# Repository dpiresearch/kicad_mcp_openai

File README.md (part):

# Discussions. Get in here.

https://github.com/mixelpixx/KiCAD-MCP-Server/discussions/73

# KiCAD MCP Server

A Model Context Protocol (MCP) server that enables AI assistants like OpenAI Codex to interact with KiCAD for PCB design automation. Built on the MCP 2025-06-18 specification, this server provides comprehensive tool schemas and real-time project state access for intelligent PCB design workflows.

## Overview

The [Model Context Protocol](https://modelcontextprotocol.io/) is an open standard that allows AI assistants to securely connect to external tools and data sources. This implementation provides a standardized bridge between OpenAI-powered MCP clients and KiCAD, enabling natural language control of PCB design operations.

**Key Capabilities:**

- 122 tools across 16 categories with JSON Schema validation
- Smart tool discovery with router pattern (reduces AI context by 70%)
- 8 dynamic resources exposing project state
- Complete schematic workflow with 27 tools and dynamic symbol loading (~10,000 symbols)
- Freerouting autorouter integration (Java, Docker, or Podman)
- Custom footprint and symbol creation tools
- JLCPCB parts integration with 2.5M+ component catalog and local library search
- Datasheet enrichment via LCSC
- Full MCP 2025-06-18 protocol compliance
- Cross-platform support (Linux, Windows, macOS)
- Real-time KiCAD UI integration via IPC API (experimental)
- Comprehensive error handling and logging

## Try out Arduino MCP - now you can get OpenAI Codex to help in the IDE, real time!:

https://github.com/mixelpixx/arduino-ide

## What's New in v2.2.3

### New Tools: FFC/Ribbon Cable Passthrough Workflow

A complete workflow for designing passthrough adapter boards (e.g. Raspberry Pi CSI
cable adapters) is now supported:

1. `connect_passthrough` — wires all pins of one connector to the matching pins of
   another in the schematic (J1 pin N → J2 pin N, auto-named nets).
2. `sync_schematic_to_board` — imports the net assignments into the PCB.
3. `route_pad_to_pad` — routes each connection with automatic via insertion when
   pads are on opposite copper layers.
4. `snapshot_project` — saves a named checkpoint into `<project>/snapshots/`.

### Bug Fixes (KiCAD 9 / Windows)

- **Via insertion for B.Cu footprints** — `route_pad_to_pad` now correctly detects
  when a footprint is on B.Cu and inserts the required via. (KiCAD 9 SWIG returned
  `F.Cu` for all SMD pads regardless of layer — fixed.)
- **Board outline rounded corners** — `add_board_outline` now correctly applies
  `cornerRadius` when `shape="rounded_rectangle"`.
- **B.Cu placement hang** — placing a footprint on B.Cu no longer causes a ~30s
  freeze in KiCAD 9.

### Developer Mode

Set `KICAD_MCP_DEV=1` in your Codex MCP server environment to automatically save
the MCP session log into the project's `logs/` folder on every `export_gerber` and
`snapshot_project` call. Useful for debugging and for attaching to GitHub issues.

```json
"env": {
  "KICAD_MCP_DEV": "1"
}
```

> **Privacy warning:** The session log contains your full tool call history
> (including file paths and design details). **Review or delete `logs/` before
> sharing a project directory publicly.**

See [CHANGELOG](CHANGELOG.md) for the full list of changes in this release.

---

## What's New in v2.1.0

### Critical Schematic Workflow Fix + Complete Wiring System (Issue #26)

The schematic workflow was completely broken in previous versions - **this is now fixed AND dramatically enhanced!**

**What was broken:**

- `create_project` only created PCB files, no schematics
- `add_schematic_component` called non-existent API methods
- Schematics couldn't be created or edited at all
- Only 13 component types available (severe limitation)
- No working wire/connection functionality

**Complete Implementation (3 Phases):**

**Phase 1: Component Placement Foundation**

- `create_project` now creates both .kicad_pcb and .kicad_sch files
- Added pre-configured template schematics with 13 common component types
- Rewrote component placement to use proper `clone()` API

**Phase 2: Dynamic Symbol Loading (BREAKTHROUGH!)**

- **Access to ALL ~10,000 KiCad symbols** from standard libraries
- Automatic detection and dynamic loading from `.kicad_sym` library files
- Zero configuration required - just specify library and symbol name
- Seamless integration with existing MCP tools
- Full S-expression parsing and injection system

**Phase 3: Intelligent Wiring System (NEW in v2.1.0)**

- **Automatic pin location discovery** with rotation support (0°, 90°, 180°, 270°)
- **Smart wire routing** (direct, orthogonal horizontal-first, orthogonal vertical-first)
- **Power symbol support** (VCC, GND, +3V3, +5V, etc.)
- **Wire graph analysis** - geometric tracing for net connectivity
- **Net label management** (local, global, hierarchical labels)
- **Netlist generation** with accurate component/pin connections

**Technical Architecture:**
The kicad-skip library cannot create symbols or wires from scratch. We implemented a comprehensive solution:

1. **Static Templates:** 13 pre-configured symbols (R, C, L, LED, etc.) for instant use
2. **Dynamic Loading:** On-demand injection of ANY symbol from KiCad libraries:
   - Parse `.kicad_sym` library files using S-expression parser
   - Inject symbol definition into schematic's `lib_symbols` section
   - Create offscreen template instance
   - Reload schematic so kicad-skip sees new template
   - Clone template to create actual component
3. **Wire Creation:** S-expression-based wire injection (bypasses kicad-skip API limitations)
4. **Pin Discovery:** Parse symbol definitions, apply rotation transformations, calculate absolute positions
5. **Connectivity Analysis:** Geometric wire tracing to build net connection graphs

**Example - Complete Circuit Creation:**

```python
# Load power symbols dynamically
loader.load_symbol_dynamically(sch_path, "power", "VCC")

# Place components with auto-rotation
ComponentManager.add_component(sch, {
    "type": "STM32F103C8Tx",
    "library": "MCU_ST_STM32F1",
    "reference": "U1",
    "x": 100, "y": 100, "rotation": 0
})

# Connect with intelligent routing
ConnectionManager.add_connection(sch_path, "U1", "1", "R1", "2", routing="orthogonal_h")

# Connect to power nets
ConnectionManager.connect_to_net(sch_path, "U1", "VDD", "VCC")

# Analyze connectivity
connections = ConnectionManager.get_net_connections(sch, "VCC", sch_path)
# Returns: [{"component": "U1", "pin": "VDD"}, {"component": "R1", "pin": "1"}]
```

**Test Results:**

- Component placement: 100% passing
- Dynamic symbol loading: 10,000+ symbols accessible
- Wire creation: 100% passing (8/8 connections in test circuit)
- Pin discovery: Rotation-aware, sub-millimeter accuracy
- Net connectivity: 100% accurate (VCC: 2 connections, GND: 4 connections)
- Netlist generation: Working with accurate pin-level connections

See [Schematic Tools Reference](docs/SCHEMATIC_TOOLS_REFERENCE.md) for the complete schematic tool documentation.

### IPC Backend (Experimental)

We are currently implementing and testing the KiCAD 9.0 IPC API for real-time UI synchronization:

- Changes made via MCP tools appear immediately in the KiCAD UI
- No manual reload required when IPC is active
- Hybrid backend: uses IPC when available, falls back to SWIG API
- IPC runtime reconnect: if MCP has fallen back to SWIG, IPC-capable board
  tools retry IPC after KiCAD launches instead of staying on SWIG for the entire
  session
- 20+ commands now support IPC including routing, component placement, and zone operations

Note: IPC features are under active development and testing. Enable IPC in KiCAD via Preferences > Plugins > Enable IPC API Server.

For OpenCode on Windows, the backend can be configured as `auto`, `ipc`, or
`swig` during setup. See [OpenCode (Windows)](#opencode-windows) for the
configuration command and backend options.

### Tool Discovery & Router Pattern

We've implemented an intelligent tool router to keep AI context efficient while maintaining full functionality:

- **18 direct tools** always visible for high-frequency operations
- **65 routed tools** organized into 8 categories (board, component, export, drc, schematic, library, routing, autoroute)
- **35 additional tools** always visible (symbol/footprint creators, JLCPCB, datasheet, advanced routing)
- **4 router tools** for discovery and execution:
  - `list_tool_categories` - Browse all available categories
  - `get_category_tools` - View tools in a specific category
  - `search_tools` - Find tools by keyword
  - `execute_tool` - Run any tool with parameters

**Why this matters:** By organizing tools into discoverable categories, OpenAI Codex can intelligently find and use the right tool for your task without loading all 122 tool schemas into every conversation. This reduces context consumption while maintaining full access to all functionality.

**Usage is seamless:** Just ask naturally - "export gerber files" or "add mounting holes" - and Codex will discover and execute the appropriate tools automatically.

### NEEDS TESTING - REPORT ISSUES

### JLCPCB Parts Integration (New!)

Complete integration with JLCPCB's parts catalog, providing two complementary approaches for component selection:

**Dual-Mode Architecture:**

1. **Local Symbol Libraries** - Search JLCPCB libraries installed via KiCAD Plugin and Content Manager (contributed by [@l3wi](https://github.com/l3wi))
2. **JLCPCB API Integration** - Access the complete 2.5M+ parts catalog with real-time pricing and stock data

**Key Features:**

- Real-time pricing with quantity breaks (1+, 10+, 100+, 1000+)
- Stock availability checking
- Basic vs Extended library type identification (Basic = free assembly)
- Intelligent cost optimization with alternative part suggestions
- Package-to-footprint mapping for KiCAD compatibility
- Parametric search by category, package, manufacturer
- Local SQLite database for fast offline searching
- No API credentials required for local library search

**Why this matters:** JLCPCB offers PCB assembly services where Basic parts have no assembly fee, while Extended parts charge $3 per unique component. This integration helps you find the cheapest components with the best availability, potentially saving hundreds of dollars on assembly costs for production runs.

See [JLCPCB Usage Guide](docs/JLCPCB_USAGE_GUIDE.md) for detailed setup and usage instructions.

### Comprehensive Tool Schemas

Every tool now includes complete JSON Schema definitions with:

- Detailed parameter descriptions and constraints
- Input validation with type checking
- Required vs. optional parameter specifications
- Enumerated values for categorical inputs
- Clear documentation of what each tool does

### Resources Capability

Access project state without executing tools:

- `kicad://project/current/info` - Project metadata
- `kicad://project/current/board` - Board properties
- `kicad://project/current/components` - Component list (JSON)
- `kicad://project/current/nets` - Electrical nets
- `kicad://project/current/layers` - Layer stack configuration
- `kicad://project/current/design-rules` - Current DRC settings
- `kicad://project/current/drc-report` - Design rule violations
- `kicad://board/preview.png` - Board visualization (PNG)

### Protocol Compliance

- Updated to MCP SDK 1.21.0 (latest)
- Full JSON-RPC 2.0 support
- Proper capability negotiation
- Standards-compliant error codes

## Available Tools

The server provides **122 tools** organized into 16 functional categories. With the router pattern, tools are automatically discovered as needed -- just ask Codex what you want to accomplish.

For the complete tool reference with access types (direct/routed/additional), see [Tool Inventory](docs/TOOL_INVENTORY.md).

### Project Management (5 tools)

- `create_project` - Initialize new KiCAD projects
- `open_project` - Load existing project files
- `save_project` - Save current project state
- `get_project_info` - Retrieve project metadata
- `snapshot_project` - Save named checkpoint snapshot

### Board Operations (12 tools)

- `set_board_size` - Configure PCB dimensions
- `add_board_outline` - Create board edge (rectangle, circle, polygon, rounded rectangle)
- `add_layer` - Add custom layers to stack
- `set_active_layer` - Switch working layer
- `get_layer_list` - List all board layers
- `get_board_info` - Retrieve board properties
- `get_board_2d_view` - Generate board preview image
- `capture_design_snapshot` - Save schematic and PCB visual snapshots for review
- `get_board_extents` - Get board bounding box
- `add_mounting_hole` - Place mounting holes
- `add_board_text` - Add text annotations
- `add_zone` - Add copper zone/pour with clearance settings
- `import_svg_logo` - Import SVG file as PCB silkscreen polygons

### Component Management (16 tools)

- `place_component` - Place single component with footprint
- `move_component` - Reposition existing component
- `rotate_component` - Rotate component by angle
- `delete_component` - Remove component from board
- `edit_component` - Modify component properties
- `find_component` - Search by reference or value
- `get_component_properties` - Query component details
- `add_component_annotation` - Add annotation/comment
- `group_components` - Group multiple components
- `replace_component` - Replace with different footprint
- `get_component_pads` - Get all pad information
- `get_component_list` - List all placed components
- `get_pad_position` - Get precise pad position
- `place_component_array` - Create component grids/patterns
- `align_components` - Align multiple components
- `duplicate_component` - Copy existing component

### Routing (13 tools)

- `add_net` - Create electrical net
- `route_trace` - Route copper traces between XY points
- `route_pad_to_pad` - Route between pads with auto-via insertion
- `add_via` - Place vias for layer transitions
- `delete_trace` - Remove traces (by UUID, position, or net)
- `query_traces` - Query/filter traces
- `get_nets_list` - List all nets with statistics
- `modify_trace` - Change trace width, layer, or net
- `create_netclass` - Define net class with rules
- `add_copper_pour` - Create copper zones/pours
- `route_differential_pair` - Route differential signals
- `refill_zones` - Refill all copper zones
- `copy_routing_pattern` - Replicate routing between component groups

### Schematic (27 tools)

Complete schematic workflow with dynamic symbol loading (~10,000 symbols) and intelligent wiring.

**Component Operations:**

- `add_schematic_component` - Place symbols from any KiCad library
- `delete_schematic_component` - Remove component
- `edit_schematic_component` - Edit footprint, value, reference, label positions, and **arbitrary custom properties** (MPN, Manufacturer, DigiKey_PN, LCSC, Voltage, Tolerance, Dielectric, …) in one batched call
- `set_schematic_component_property` - Add or update a single custom property (BOM/sourcing field) on a component
- `remove_schematic_component_property` - Delete a single custom property from a component
- `get_schematic_component` - Inspect every field on a component (built-in + custom) including label positions
- `list_schematic_components` - List all components
- `move_schematic_component` - Reposition component
- `rotate_schematic_component` - Rotate component
- `annotate_schematic` - Auto-assign reference designators

**Wiring and Connections:**

- `add_wire` - Create wire between points
- `delete_schematic_wire` - Remove wire segment
- `add_schematic_connection` - Auto-connect pins with routing
- `add_schematic_net_label` - Add net labels (VCC, GND, signals)
- `delete_schematic_net_label` - Remove net label
- `connect_to_net` - Connect pin to named net
- `connect_passthrough` - Wire all matching pins between connectors (FFC/ribbon)
- `get_schematic_pin_locations` - Get pin locations for component

**Analysis and Export:**

- `get_net_connections` - Trace net connectivity
- `list_schematic_nets` / `list_schematic_wires` / `list_schematic_labels`
- `create_schematic` - Create new schematic file
- `get_schematic_view` - Rasterized schematic preview
- `export_schematic_svg` / `export_schematic_pdf`
- `run_erc` - Electrical rule check
- `generate_netlist` - Generate netlist from schematic
- `sync_schematic_to_board` - Import nets/pads to PCB (F8 equivalent)

See [Schematic Tools Reference](docs/SCHEMATIC_TOOLS_REFERENCE.md) for details and examples.

### Design Rules / DRC (8 tools)

- `set_design_rules` / `get_design_rules` - Configure and inspect rules
- `run_drc` - Execute design rule check
- `get_drc_violations` - Get violation list by severity
- `add_net_class` / `assign_net_to_class` - Net class management
- `set_layer_constraints` / `check_clearance` - Layer and clearance rules

### Export (8 tools)

- `export_gerber` - Gerber fabrication files
- `export_pdf` / `export_svg` - Documentation and vector graphics
- `export_3d` - 3D models (STEP, STL, VRML, OBJ)
- `export_bom` - Bill of materials (CSV, XML, HTML, JSON)
- `export_netlist` - Netlist (KiCad, Spice, Cadstar, OrcadPCB2)
- `export_position_file` - Component positions for pick and place
- `export_vrml` - VRML 3D model

### Footprint Libraries (4 tools) and Symbol Libraries (4 tools)

- `list_libraries` / `list_symbol_libraries` - Browse available libraries
- `search_footprints` / `search_symbols` - Search across all libraries
- `list_library_footprints` / `list_library_symbols` - Browse specific library
- `get_footprint_info` / `get_symbol_info` - Detailed information

### Footprint Creator (4 tools) and Symbol Creator (4 tools)

Create custom components when existing libraries do not have what you need.

- `create_footprint` / `create_symbol` - Build from scratch with pads/pins
- `edit_footprint_pad` - Modify pad properties
- `register_footprint_library` / `register_symbol_library` - Register in lib-table
- `list_footprint_libraries` / `list_symbols_in_library` - Browse custom libraries
- `delete_symbol` - Remove symbol from library

See [Footprint and Symbol Creator Guide](docs/FOOTPRINT_SYMBOL_CREATOR_GUIDE.md) for details.

### Datasheet Tools (2 tools)

- `enrich_datasheets` - Auto-populate datasheet URLs using LCSC part numbers
- `get_datasheet_url` - Get LCSC datasheet URL for a component

### JLCPCB Integration (5 tools)

- `download_jlcpcb_database` - Download 2.5M+ parts catalog (one-time setup)
- `search_jlcpcb_parts` - Search with parametric filters
- `get_jlcpcb_part` - Detailed part info with pricing
- `get_jlcpcb_database_stats` - Database statistics
- `suggest_jlcpcb_alternatives` - Find cheaper or in-stock alternatives

### Freerouting Autorouter (4 tools)

- `autoroute` - Run Freerouting autorouter (DSN export, route, SES import)
- `export_dsn` / `import_ses` - Manual Specctra DSN/SES workflow
- `check_freerouting` - Verify Java and Freerouting availability

See [Freerouting Guide](docs/FREEROUTING_GUIDE.md) for setup and usage.

### UI Management (2 tools)

- `check_kicad_ui` - Check if KiCAD is running
- `launch_kicad_ui` - Launch KiCAD application

## Prerequisites

### Required Software

**KiCAD 9.0 or higher**

- Download from [kicad.org/download](https://www.kicad.org/download/)
- Must include Python module (pcbnew)
- Verify installation:
  ```bash
  python3 -c "import pcbnew; print(pcbnew.GetBuildVersion())"
  ```

**Node.js 18 or Higher**

- Download from [nodejs.org](https://nodejs.org/)
- Verify: `node --version` and `npm --version`

**Python 3.9 or Higher**

- Comes bundled with KiCAD (macOS builds ship Python 3.9; Linux/Windows builds ship Python 3.11)
- Required packages (auto-installed):
  - kicad-python (kipy) >= 0.5.0 (IPC API support, optional but recommended)
  - kicad-skip >= 0.1.0 (schematic support)
  - Pillow >= 9.0.0 (image processing)
  - cairosvg >= 2.7.0 (SVG rendering)
  - colorlog >= 6.7.0 (logging)
  - pydantic >= 2.5.0 (validation)
  - requests >= 2.32.5 (HTTP client)
  - python-dotenv >= 1.0.0 (environment)

**MCP Client**
Choose one:

- [OpenAI Codex CLI](https://developers.openai.com/codex) - Official OpenAI CLI with MCP support
- [Cline](https://github.com/cline/cline) - VSCode extension
- [OpenCode](https://opencode.ai/) - Terminal-based AI coding agent with MCP support

### Supported Platforms

- **Linux** (Ubuntu 22.04+, Fedora, Arch) - Primary platform, fully tested
- **Windows 10/11** - Fully supported with automated setup
- **macOS** - Experimental support

## Installation

### Linux (Ubuntu/Debian)

```bash
# Install KiCAD 9.0 or higher
sudo add-apt-repository --yes ppa:kicad/kicad-9.0-releases
sudo apt-get update
sudo apt-get install -y kicad kicad-libraries

# Install Node.js
curl -fsSL https://deb.nodesource.com/setup_20.x | sudo -E bash -
sudo apt-get install -y nodejs

# Clone and build
git clone https://github.com/mixelpixx/KiCAD-MCP-Server.git
cd KiCAD-MCP-Server
npm install
pip3 install -r requirements.txt
npm run build

# Verify
python3 -c "import pcbnew; print(pcbnew.GetBuildVersion())"
```

### Windows 10/11

**Automated Setup (Recommended):**

```powershell
git clone https://github.com/mixelpixx/KiCAD-MCP-Server.git
cd KiCAD-MCP-Server
.\setup-windows.ps1
```

The script will:

- Detect KiCAD installations, including both machine-wide installs under
  `C:\Program Files\KiCad` and per-user installs under
  `%LOCALAPPDATA%\Programs\KiCad`
- Verify prerequisites
- Install dependencies
- Build project
- Generate configuration
- Run diagnostics

**Manual Setup:**
See [Windows Installation Guide](docs/WINDOWS_SETUP.md) for detailed instructions.

### macOS

**Important:** On macOS, use KiCAD's bundled Python to ensure proper access to the `pcbnew` module.

#### Manual Setup

```bash
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
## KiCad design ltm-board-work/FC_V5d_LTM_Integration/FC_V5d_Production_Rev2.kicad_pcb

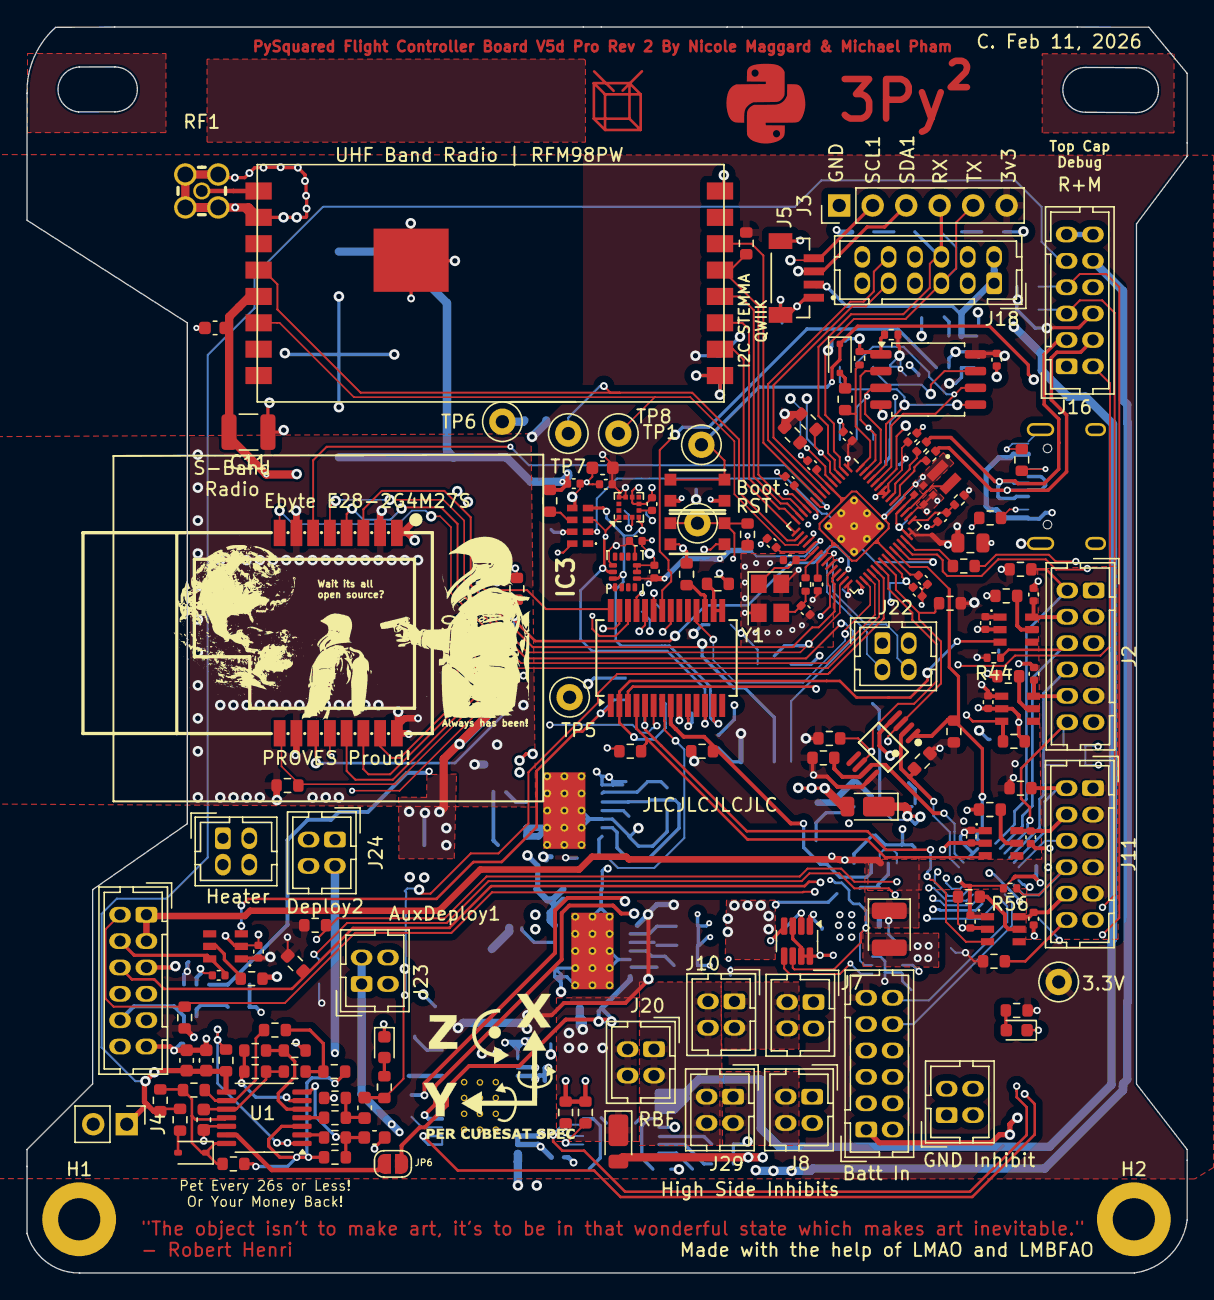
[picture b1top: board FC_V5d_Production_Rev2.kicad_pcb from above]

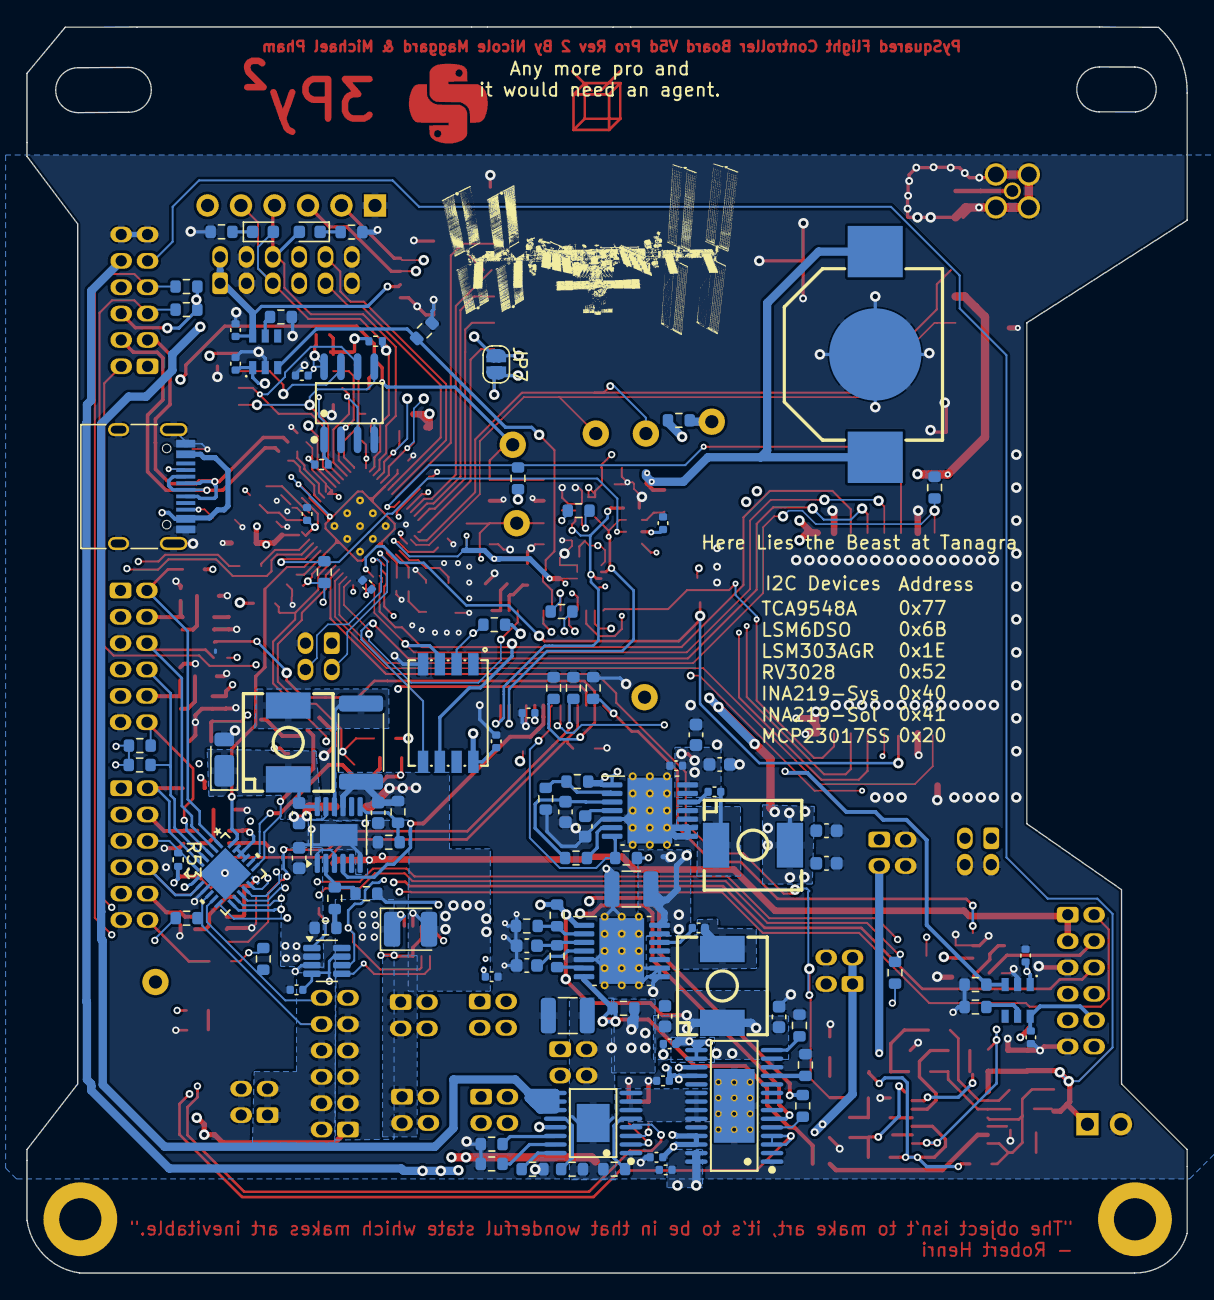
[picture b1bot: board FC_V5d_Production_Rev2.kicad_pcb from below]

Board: 4 copper layers, 88.0 x 94.5 mm, 257 parts (103 on the bottom side), 179 nets.

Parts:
BT1: MY-1220-03; BAT-SMD_MY-1220-03
C1, C3, C14, C20, C21, C22, C23, C24, C40, C42, C43: 10uF; C_0603_1608Metric
C2, C10, C67, C70, C71, C72, C73, C74, C76, C77, C78: 100n; C_0402_1005Metric
C4, C37, C41: 1uF; C_0603_1608Metric
C5, C6, C18, C26, C27, C28, C29, C30, C32, C34, C35, C38, C39, C44, C47, C48, C49, C50, C51, C52, C53, C55, C59, C60, C79, C80: 100nf; C_0402_1005Metric
C7, C8, C15, C16: 22uF; C_0603_1608Metric
C9, C36: 3.3nF; C_0603_1608Metric
C11, C19, C25: 100uF; C_1210_3225Metric
C31, C54, C56, C57, C58: 220nf; C_0402_1005Metric
C63, C64: 15p; C_0402_1005Metric
C65, C66: 4.7u; C_0402_1005Metric_small_pads
C68, C69: 4.7u; C_0402_1005Metric
C75: 10u; C_0805_2012Metric
D1, D2, D3: LED; LED_0603_1608Metric
D4: NSR0320; D_SOD-323F
D6: GREEN; LED_0603_1608Metric
D7: 1N4151WS; D_SOD-323
D12, D15: DFLS130L; D_PowerDI-123
D13: DFLS130L-7; D_PowerDI-123
H1, H2: MountingHole; MountingHole_3.2mm_M3_DIN965_Pad
IC3: RV-3028-C7_32.768kHz_1ppm_TA_QC; RV3028C7
IC6: LT3652IMSE#PBF; MSOP-12-1EP_3x4mm_P0.65mm_EP1.65x2.85mm
J2, J11: DF11CZ-12DP-2V(27); Hirose_DF11-12DP-2DSA_2x06_P2.00mm_Vertical
J3: Life Makes Lemonade; PinHeader_1x06_P2.54mm_Vertical
J4: Conn_01x02; PinHeader_1x02_P2.54mm_Vertical
J5: BM04B-SRSS-TB(LF)(SN); JST_BM04B-SRSS-TB(LF)(SN)
J7: INHIBIT_P1; Hirose_DF11-4DP-2DSA_2x02_P2.00mm_Vertical
J8: INHIBIT_S1; Hirose_DF11-4DP-2DSA_2x02_P2.00mm_Vertical
J10: INHIBIT_P2; Hirose_DF11-4DP-2DSA_2x02_P2.00mm_Vertical
J12: USB_C_Receptacle_USB2.0_16P; USB_C_Receptacle_HRO_TYPE-C-31-M-12
J14: Battery Input; Hirose_DF11-12DP-2DSA_2x06_P2.00mm_Vertical
J16: DEBUG; Hirose_DF11-12DP-2DSA_2x06_P2.00mm_Vertical
J17: Face4 (Z- Face); Hirose_DF11-12DP-2DSA_2x06_P2.00mm_Vertical
J18: Payload; Hirose_DF11-12DP-2DSA_2x06_P2.00mm_Vertical
J19: ISS_INHIBIT; Hirose_DF11-4DP-2DSA_2x02_P2.00mm_Vertical
J20: RBF_Inhibit; Hirose_DF11-4DP-2DSA_2x02_P2.00mm_Vertical
J21: Heater Output; Hirose_DF11-4DP-2DSA_2x02_P2.00mm_Vertical
J22: SWD Port; Hirose_DF11-4DP-2DSA_2x02_P2.00mm_Vertical
J23: Aux Deploy 1; Hirose_DF11-4DP-2DSA_2x02_P2.00mm_Vertical
J24: Deploy 2; Hirose_DF11-4DP-2DSA_2x02_P2.00mm_Vertical
J29: INHIBIT_S2; Hirose_DF11-4DP-2DSA_2x02_P2.00mm_Vertical
JP6, JP7: SolderJumper_2_Open; SolderJumper-2_P1.3mm_Open_RoundedPad1.0x1.5mm
L1: SPM6530T-100M; IND-SMD_L7.1-W6.5-P5.60
L3: 3.3u; L_pol_2016
L4: SPM6530T-3R3M-HZ; IND-SMD_L7.1-W6.5
L5: SPM6530T-4R7M-HZ; IND-SMD_L7.1-W6.5-P5.60
R1, R5, R11, R13, R14, R16, R17, R18, R22, R24, R28, R52, R83, R84, R90, R98, R99, R107, R124, R125: 10k; R_0603_1608Metric
R2, R37: 10k; R_0402_1005Metric
R3, R4, R10, R29, R31, R64, R81, R102: 1k; R_0603_1608Metric
R6, R25, R39, R41, R45, R57, R58, R59, R60, R61, R62, R72, R73, R88, R89, R105, R106: 4.7k; R_0603_1608Metric
R7, R8: 22; R_0402_1005Metric
R9: DNF; R_0402_1005Metric
R15, R70: 10K; R_0603_1608Metric
R19, R20, R21: 3.0k; R_0603_1608Metric
R23: 121k; R_0603_1608Metric
R26, R27: 5.1k; R_0603_1608Metric
R30, R32, R33, R34, R36, R66, R67, R68, R76, R77, R78, R79, R80, R87, R92, R95, R96, R101: 100k; R_0603_1608Metric
R35: 4.7M; R_0603_1608Metric
R38: 73.2K; R_0603_1608Metric
R40, R42: 22.1K; R_0603_1608Metric
R43, R63, R65: 100K; R_0603_1608Metric
R44, R53, R56: 4.7k; R_0402_1005Metric
R46, R47, R48, R49, R50, R51, R86: 47k; R_0603_1608Metric
R54, R55, R82, R85: 15k; R_0603_1608Metric
R69: 94k; R_0603_1608Metric
R71: 634k; R_0603_1608Metric
R74: 412k; R_0603_1608Metric
R75: 0.1; R_2512_6332Metric
R91: 0; R_0402_1005Metric
R93: 1k; R_0402_1005Metric
R94: 33; R_0402_1005Metric
R100, R103, R104: 4.7K; R_0603_1608Metric
R108, R109: 2mOhm; LED_1210_3225Metric
RF1: KH-MMCX-Z; MMCX-TH_KH-MMCX-Z
SW1, SW2: KMR2; BTN_KMR2_4.6X2.8
TP1: USBBOOT; TestPoint_Loop_D1.80mm_Drill1.0mm_Beaded
TP2, TP6, TP7, TP8: RESET; TestPoint_Loop_D1.80mm_Drill1.0mm_Beaded
TP3, TP5: TestPoint; TestPoint_Loop_D1.80mm_Drill1.0mm_Beaded
U1: TLV1704; TSSOP-14_4.4x5mm_P0.65mm
U2: ZDSD04GLGEAG; LGA-8_L8.0-W6.0-P1.27-TL-1
U4: RFM98PW
U5: APS1604M-3SQR-SN_C18214056; SOIC-8_L4.9-W3.9-P1.27-LS6.0-BL
U6: TPS4H160AQPWPRQ1; HTSSOP-28_L9.7-W4.4-P0.65-LS6.4-BL-EP
U7: LSM6DSOTR; LGA-14_3x2.5mm_P0.5mm_LayoutBorder3x4y
U8, U16: INA219AxDCN; SOT-23-8
U9: MCP23017_SS; SSOP-28_5.3x10.2mm_P0.65mm
U10: TPS54226PWPRPWP14_2P31X2P46-L; HTSSOP-14-1EP_4.4x5mm_P0.65mm_EP3.4x5mm_Mask3x3.1mm_Thermal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
U11: W25Q128JVS; SOIC-8_5.3x5.3mm_P1.27mm
U12: TCA9548ARGERQ1; QFN_GERQ1_TEX
U13: TPS54225PWPR; HTSSOP-14-1EP_4.4x5mm_P0.65mm_EP3.4x5mm_Mask3x3.1mm_Thermal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
U14: TCA4307DGKR; VSSOP-8_L3.0-W3.0-P0.65-LS4.9-BL
U15: LIS2MDL; LGA-12_2x2mm_P0.5mm
U18: RP2350_60QFN; RP2350-QFN-60-1EP_7x7_P0.4mm_EP3.4x3.4mm_ThermalVias
U19, U21, U22, U23, U24, U27, U29: AP22653AW6-7; SOT26
U25: TPS2HB50AQPWPRQ1; HTSSOP-16_L5.0-W4.4-P0.65-LS6.4-BL-EP-2
U30: E28-2G4M27S; WIRELM-SMD_E28-2G4M2XS
Y1: ABM8-272-T3; Crystal_SMD_3225-4Pin_3.2x2.5mm

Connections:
+1V1: C66.1, C67.1, C69.1, C70.1, L3.1, U18.6 (DVDD), U18.23 (DVDD), U18.39 (DVDD), U18.50 (VREG_FB)
+3V3: C2.1, C10.1, C15.2, C16.2, C18.1, C28.1, C29.2, C30.1, C32.1, C34.1, C35.1, C38.1, C39.1, C43.2, C47.1, C49.1, C50.1, C53.1, C59.1, C65.1, C71.1, C72.1, C73.1, C74.1, C75.1, C76.1, C77.1, C78.1, C79.1, IC3.7 (VDD), J3.6, J14.11, J16.6, JP7.1 (A), L4.1, R1.1, R2.1, R5.2, R6.2, R11.2, R13.1, R14.2, R15.1, R25.2, R37.1, R38.2, R39.2, R41.2, R44.2, R45.2, R53.2, R56.2, R57.2, R58.2, R59.2, R60.2, R61.2, R62.2, R70.1, R72.2, R73.2, R80.1, R88.2, R89.2, R90.2, R92.1, R94.1, R98.2, R99.2, R105.2, R106.2, R107.2, R125.1, TP3.1, U2.8 (VDD), U5.8 (VDD), U7.1 (SDO/SA0), U7.5 (VDDIO), U7.8 (VDD), U7.12 (CS), U8.4 (VS), U8.7 (A0), U9.9 (VDD), U10.1 (VO), U11.8 (VCC), U12.18 (A2), U12.21 (VCC), U12.22 (A0), U12.23 (A1), U14.8 (VCC), U15.9 (Vdd), U15.10 (Vdd_IO), U16.4 (VS), U18.1 (IOVDD), U18.11 (IOVDD), U18.20 (IOVDD), U18.30 (IOVDD), U18.38 (IOVDD), U18.44 (ADC_AVDD), U18.45 (IOVDD), U18.49 (VREG_VIN), U18.53 (USB_OTP_VDD), U18.54 (QSPI_IOVDD), U19.1 (Input), U21.1 (Input), U22.1 (Input), U23.1 (Input), U24.1 (Input), U27.1 (Input), U29.1 (Input), U30.1 (VCC)
/Power Systems/3v3SW: C27.1, L4.2, U10.10 (SW1), U10.11 (SW2)
/Power Systems/5vSW: C5.2, L5.1, U13.10 (SW1), U13.11 (SW2)
/Power Systems/B-: J14.2, J14.4, J14.6, J14.8, J19.1, J19.3
/Power Systems/INHIB_1: J8.2, J8.4, J29.1, J29.3
/Power Systems/INHIB_2: J7.2, J7.4, J10.1, J10.3
/Power Systems/IN_RBF: J10.2, J10.4, J20.1, J20.3, J29.2, J29.4
/Power Systems/Load Switches/Deploy1_EN: R104.1, U6.3 (IN1), U6.4 (IN2)
/Power Systems/Load Switches/Deploy2_EN: R103.1, U6.6 (IN4)
/Power Systems/Load Switches/Heater_EN: R100.1, U6.5 (IN3)
/Power Systems/Load Switches/High Power Interstage: U6.20 (VS), U6.21 (VS), U6.22 (VS), U6.23 (VS), U25.6 (VOUT1), U25.7 (VOUT1), U25.8 (VOUT1)
/Power Systems/Load Switches/ILIM1: R84.2, U25.5 (ILIM1)
/Power Systems/Load Switches/ILIM2: R83.2, U25.12 (ILIM2)
/Power Systems/VBATT_SENSE: C42.1, D12.2 (A), IC6.9 (BAT), J7.1, J7.3, J8.1, J8.3, R71.2, R75.1, R109.2, U16.2 (IN-)
/Power Systems/V_SOLAR_SENSE: C40.1, IC6.1 (VIN), IC6.3 (~SHDN), R65.1, R108.2, U8.2 (IN-)
/RF1_ANT: RF1.5, U4.1 (ANT)
/RP2350AHHHHHHHHH/FLASH_SS: R2.2, R9.2, R91.2, U11.1 (~CS)
/RP2350AHHHHHHHHH/PSRAM_CS: R37.2, U5.1 (~CE), U18.12 (GPIO8)
/RP2350AHHHHHHHHH/QSPI_SCLK: U5.6 (SCLK), U11.6 (CLK), U18.56 (QSPI_SCLK)
/RP2350AHHHHHHHHH/QSPI_SD0: U5.5 (SI/SIO[0]), U11.5 (DI(IO0)), U18.57 (QSPI_SD0)
/RP2350AHHHHHHHHH/QSPI_SD1: U5.2 (SO/SIO[1]), U11.2 (DO(IO1)), U18.59 (QSPI_SD1)
/RP2350AHHHHHHHHH/QSPI_SD2: U5.3 (SIO[2]), U11.3 (IO2), U18.58 (QSPI_SD2)
/RP2350AHHHHHHHHH/QSPI_SD3: U5.7 (SIO[3]), U11.7 (IO3), U18.55 (QSPI_SD3)
/RP2350AHHHHHHHHH/VREG_AVDD: C68.1, R94.2, U18.46 (VREG_AVDD)
/RP2350AHHHHHHHHH/VREG_LX: L3.2, U18.48 (VREG_LX)
/RP2350AHHHHHHHHH/XIN: C63.1, U18.21 (XIN), Y1.1
/RP2350AHHHHHHHHH/XOUT: R93.1, U18.22 (XOUT)
/Watchdog Circuit/WDT-VP: R19.2, R20.1, U1.5 (+)
BATT_SCL: J14.12, R89.1, U12.11 (SC4)
BATT_SDA: J14.10, R88.1, U12.10 (SD4)
BOOTSEL: R10.1, R91.1, U18.60 (QSPI_SS)
DEPLOY1: C54.1, J16.10, U6.27 (OUT1), U6.28 (OUT1)
DEPLOY1_AUX: C56.1, J23.1, J23.3, U6.25 (OUT2), U6.26 (OUT2)
DEPLOY2: C57.1, J24.1, J24.3, U6.17 (OUT3), U6.18 (OUT3)
Dir_Chrg_In: J14.1, J14.3, J14.5, J14.7, J14.9, J16.8, R109.1, U16.1 (IN+)
ENABLE_Heater: R100.2, U9.21 (GPA0)
F0_PWR: C44.1, J2.4, U19.6 (Output)
F0_SCL: J2.6, R44.1, U12.2 (SC0)
F0_SDA: J2.2, R62.1, U12.1 (SD0)
F1_PWR: C48.1, J2.10, U21.6 (Output)
F1_SCL: J2.8, R45.1, U12.4 (SC1)
F1_SDA: J2.12, R61.1, U12.3 (SD1)
F2_PWR: C51.1, J11.4, U22.6 (Output)
F2_SCL: J11.6, R53.1, U12.6 (SC2)
F2_SDA: J11.2, R60.1, U12.5 (SD2)
F3_PWR: C55.1, J11.10, U24.6 (Output)
F3_SCL: J11.8, R56.1, U12.8 (SC3)
F3_SDA: J11.12, R59.1, U12.7 (SD3)
F4_PWR: C52.1, J17.4, U23.6 (Output)
F4_SCL: J17.6, R57.1, U12.13 (SC5)
F4_SDA: J17.2, R58.1, U12.12 (SD5)
F5_PWR: C60.1, J17.10, U27.6 (Output)
F5_SCL: J17.12, R72.1, U12.15 (SC6)
F5_SDA: J17.8, R73.1, U12.14 (SD6)
FACE0_ENABLE: R67.2, U9.2 (GPB1), U19.3 (EN)
FACE1_ENABLE: R68.2, U9.3 (GPB2), U21.3 (EN)
FACE2_ENABLE: R76.2, U9.4 (GPB3), U22.3 (EN)
FACE3_ENABLE: R78.2, U9.5 (GPB4), U24.3 (EN)
FACE4_ENABLE: R77.2, U9.1 (GPB0), U23.3 (EN)
FACE5_ENABLE: R87.2, U9.6 (GPB5), U27.3 (EN)
FC_RESET: J16.2, J22.1, R1.2, SW2.A, SW2.A' (P1), TP2.1, U18.26 (RUN)
FIRE_DEPLOY1_A: U18.42 (GPIO28_ADC2), U25.4 (EN1)
FIRE_DEPLOY1_B: R104.2, U18.43 (GPIO29_ADC3)
FIRE_DEPLOY2_B: R103.2, U9.23 (GPA2)
GND: BT1.3 (-), C1.2, C2.2, C3.2, C4.2, C6.1, C7.2, C8.2, C9.1, C10.2, C11.1, C14.1, C15.1, C16.1, C18.2, C19.2, C21.1, C22.1, C23.1, C24.1, C25.2, C26.2, C28.2, C29.1, C30.2, C31.2, C32.2, C34.2, C35.2, C36.2, C37.2, C38.2, C39.2, C40.2, C42.2, C43.1, C44.2, C47.2, C48.2, C49.2, C50.2, C51.2, C52.2, C53.2, C54.2, C55.2, C56.2, C57.2, C58.2, C59.2, C60.2, C63.2, C64.2, C65.2, C66.2, C67.2, C68.2, C69.2, C70.2, C71.2, C72.2, C73.2, C74.2, C75.2, C76.2, C77.2, C78.2, C79.2, C80.2, D3.1 (K), D6.1 (K), D13.2 (A), IC3.5 (VSS), IC6.6 (TIMER), IC6.13 (EP), J2.5, J2.11, J3.1, J4.2, J5.1, J5.S1 (SHIELD), J5.S2 (SHIELD), J11.5, J11.11, J12.A1 (GND), J12.A12 (GND), J12.B1 (GND), J12.B12 (GND), J12.S1 (SHIELD), J16.11, J16.12, J17.5, J17.11, J18.3, J18.4, J18.11, J18.12, J19.2, J19.4, J21.2, J21.4, J22.3, J23.2, J23.4, J24.2, J24.4, R3.2, R4.2, R20.2, R22.2, R24.1, R26.1, R27.1, R40.1, R42.2, R46.1, R47.1, R48.1, R49.1, R50.1, R51.1, R52.1, R54.1, R55.2, R67.1, R68.1, R69.1, R74.1, R76.1, R77.1, R78.1, R79.1, R81.2, R82.1, R85.1, R86.1, R87.1, R95.2, R96.2, R101.2, R102.2, RF1.1, RF1.2, RF1.3, RF1.4, SW1.B (S), SW1.B' (S1), SW2.B (S), SW2.B' (S1), U1.12 (V-), U2.4 (GND), U4.2 (GND), U4.16 (GND), U4.17 (GND), U5.4 (VSS), U6.1 (GND), U6.12 (GND), U6.13 (THER), U6.29 (EP), U7.6 (GND), U7.7 (GND), U8.3 (GND), U8.8 (A1), U9.10 (VSS), U10.5 (GND), U10.8 (PGND1), U10.9 (PGND2), U10.15 (EPAD), U11.4 (GND), U12.9 (GND_2), U12.25 (GND), U13.5 (GND), U13.8 (PGND1), U13.9 (PGND2), U13.15 (EPAD), U14.4 (GND), U15.6 (GND), U15.8 (GND), U16.3 (GND), U16.7 (A0), U16.8 (A1), U18.47 (VREG_PGND), U18.61 (GND), U19.2 (GND), U21.2 (GND), U22.2 (GND), U23.2 (GND), U24.2 (GND), U25.1 (GND), U27.2 (GND), U29.2 (GND), U30.2 (GND), U30.7 (GND), U30.10 (GND), U30.16 (GND), Y1.2, Y1.4
Heater Output: C58.1, J21.1, J21.3, U6.15 (OUT4), U6.16 (OUT4)
unnamed: BT1.1 (+), BT1.2 (+), C26.1, R64.2
unnamed: C20.2, R22.1, R28.1
unnamed: C64.1, R93.2, Y1.3
unnamed: D1.1 (K), R4.1
unnamed: D2.1 (K), R3.1
unnamed: D3.2 (A), R80.2
unnamed: D4.2 (A), R10.2
unnamed: D6.2 (A), R21.2
unnamed: D7.2, R33.1
unnamed: C41.2, D12.1 (K), IC6.11 (BOOST)
unnamed: C41.1, D13.1 (K), IC6.12 (SW), L1.1
unnamed: IC3.8 (EVI), R14.1, TP6.1
unnamed: IC3.6 (VBACKUP), R64.1
unnamed: IC6.10 (SENSE), L1.2, R75.2
unnamed: IC6.7 (VFB), R71.1, R74.2
unnamed: IC6.2 (VIN_REG), R66.2, R69.2
unnamed: J12.A5 (CC1), R26.2
unnamed: J12.B5 (CC2), R27.2
unnamed: JP6.1 (A), U1.13
unnamed: JP7.2 (B), U4.9 (3.3V)
unnamed: R16.2, R17.1, R32.2
unnamed: R29.1, U1.2
unnamed: R31.1, U1.1
unnamed: R65.2, R66.1
unnamed: R28.2, U1.4 (-)
unnamed: C21.2, R29.2, R30.2, U1.7 (+)
unnamed: R18.2, R19.1, U1.6 (-)
unnamed: R32.1, R34.1, U1.9 (+)
unnamed: D7.1, R34.2, R35.1, R36.1, U1.11 (+), U1.14
unnamed: C24.2, R17.2, R18.1, U1.10 (-)
unnamed: R102.1, U6.11 (CL)
unnamed: R101.1, U6.14 (DIAG_EN)
unnamed: R24.2, U9.15 (A0), U9.16 (A1)
unnamed: R52.2, U9.17 (A2)
unnamed: R43.1, U10.6 (PG)
unnamed: C36.1, U10.4 (SS)
unnamed: C27.2, U10.12 (VBST)
unnamed: R38.1, R40.2, U10.2 (VFB)
unnamed: C37.1, R43.2, U10.3 (VREG5)
unnamed: R98.1, U12.19 (SCL), U14.2 (SCLOUT)
unnamed: R99.1, U12.20 (SDA), U14.7 (SDAOUT)
unnamed: R63.2, U13.6 (PG)
unnamed: C9.2, U13.4 (SS)
unnamed: C5.1, U13.12 (VBST)
unnamed: R23.2, R42.1, U13.2 (VFB)
unnamed: C4.1, R63.1, U13.3 (VREG5)
unnamed: C31.1, U15.5 (C1)
unnamed: R107.1, U15.3 (~CS)
unnamed: R46.2, U19.5 (ILIM)
unnamed: R51.2, U21.5 (ILIM)
unnamed: R47.2, U22.5 (ILIM)
unnamed: R48.2, U23.5 (ILIM)
unnamed: R49.2, U24.5 (ILIM)
unnamed: R55.1, U25.16 (DIA_EN)
unnamed: R54.2, U25.3 (LATCH)
unnamed: R85.2, U25.14 (SEL1)
unnamed: R82.2, U25.15 (SEL2)
unnamed: R81.1, U25.2 (SNS)
unnamed: R86.2, U27.5 (ILIM)
unnamed: R50.2, U29.5 (ILIM)
PAYLOAD_BATT: J18.7, J18.8, U25.9 (VOUT2), U25.10 (VOUT2), U25.11 (VOUT2)
PAYLOAD_BATT_ENABLE: U9.24 (GPA3), U25.13 (EN2)
PAYLOAD_PWR: C80.1, J5.2, J18.1, J18.2, U29.6 (Output)
PAYLOAD_PWR_ENABLE: R79.2, U9.22 (GPA1), U29.3 (EN)
RF1_IO0: TP8.1, U4.6 (GPIO_0), U18.18 (GPIO14)
RF1_IO4: TP7.1, U4.4 (GPIO_4), U18.17 (GPIO13)
RF1_RST: U4.14 (RESET), U18.9 (GPIO6)
RF2_IO0: U9.27 (GPA6), U30.12 (BUSY)
RF2_IO1: U9.26 (GPA5), U30.13 (DIO1)
RF2_IO2: U9.25 (GPA4), U30.14 (DIO2)
RF2_IO3: U9.28 (GPA7), U30.15 (DIO3)
RF2_RST: R92.2, U18.28 (GPIO17), U30.11 (NRESET)
RF2_RX_EN: R96.1, U18.33 (GPIO21), U30.8 (RX_EN)
RF2_TX_EN: R95.1, U18.34 (GPIO22), U30.9 (TX_EN)
RF_VCC: C7.1, C8.1, C11.2, C14.2, L5.2, R23.1, TP5.1, U4.5 (VCC), U13.1 (VO)
RTC_INT: IC3.2 (~INT), R5.1, U18.41 (GPIO27_ADC1)
RX0: D2.2 (A), J3.4, J18.6, U18.3 (GPIO1)
RX1: J18.10, U18.8 (GPIO5)
SCL0: R6.1, U8.5 (SCL), U14.3 (SCLIN), U16.5 (SCL), U18.37 (GPIO25)
SCL1: IC3.3 (SCL), J3.2, J5.4, R39.1, U7.13 (SCL), U9.12 (SCK), U15.1 (SCL/SPC), U18.5 (GPIO3)
SCL_Top: J16.7, R105.1, U12.17 (SC7)
SDA0: R25.1, U8.6 (SDA), U14.6 (SDAIN), U16.6 (SDA), U18.36 (GPIO24)
SDA1: IC3.4 (SDA), J3.3, J5.3, R41.1, U7.14 (SDA), U9.13 (SDA), U15.4 (SDA/SDI/SDO), U18.4 (GPIO2)
SDA_Top: J16.5, R106.1, U12.16 (SD7)
SPI0_CS0: R13.2, U4.13 (NSS), U18.13 (GPIO9)
SPI0_MISO: U4.10 (MISO), U18.16 (GPIO12)
SPI0_MOSI: U4.11 (MOSI), U18.15 (GPIO11)
SPI0_SCK: U4.12 (SCK), U18.14 (GPIO10)
SPI1_CS0: R90.1, U18.10 (GPIO7), U30.6 (NSS_CTS)
SPI1_CS1: R11.1, U2.2 (DAT3), U18.19 (GPIO15)
SPI1_MISO: U2.6 (DAT0), U18.27 (GPIO16), U30.3 (MISO_TX)
SPI1_MOSI: U2.5 (CMD), U18.31 (GPIO19), U30.4 (MOSI_RX)
SPI1_SCK: U2.3 (CLK), U18.29 (GPIO18), U30.5 (SCK_RTSN)
SWCLK: J22.2, U18.24 (SWCLK)
SWDIO: J22.4, U18.25 (SWD)
TX0: D1.2 (A), J3.5, J18.5, R9.1, U18.2 (GPIO0)
TX1: J18.9, U18.7 (GPIO4)
USBBOOT: D4.1 (K), J16.1, SW1.A, SW1.A' (P1), TP1.1
USB_D+: J12.A6 (D+), J12.B6 (D+), J16.3, R8.2
USB_D-: J12.A7 (D-), J12.B7 (D-), J16.4, R7.2
USB_DM: R7.1, U18.51 (USB_DM)
USB_DP: R8.1, U18.52 (USB_DP)
VBUS: D15.2 (A), J12.A4 (VBUS), J12.A9 (VBUS), J12.B4 (VBUS), J12.B9 (VBUS)
VBUSP: C1.1, C3.1, C6.2, C19.1, C25.1, D15.1 (K), J20.2, J20.4, R16.1, R30.1, R36.2, R83.1, R84.1, R124.1, U1.3 (V+), U10.13 (VIN), U10.14 (VCC), U13.13 (VIN), U13.14 (VCC), U25.17 (VBB)
VSOLAR: J2.1, J2.3, J2.7, J2.9, J11.1, J11.3, J11.7, J11.9, J17.1, J17.3, J17.7, J17.9, R108.1, U8.1 (IN+)
WDT_DISABLE: C22.2, C23.2, J4.1, J16.9, R31.2, R33.2, R35.2, U1.8 (-)
WDT_WDI: C20.1, R21.1, U18.35 (GPIO23)
~3v3_RESET: JP6.2 (B), R124.2, U10.7 (EN)
~5V_RESET: R125.2, U9.7 (GPB6), U13.7 (EN)
~CHARGE: IC6.4 (~CHRG), R70.2, U9.8 (GPB7)
~GPIO_EXPANDER_RESET: U9.18 (~RESET), U18.32 (GPIO20)
~MUX_RESET: R15.2, U12.24 (RESET), U14.1 (EN), U18.40 (GPIO26_ADC0)

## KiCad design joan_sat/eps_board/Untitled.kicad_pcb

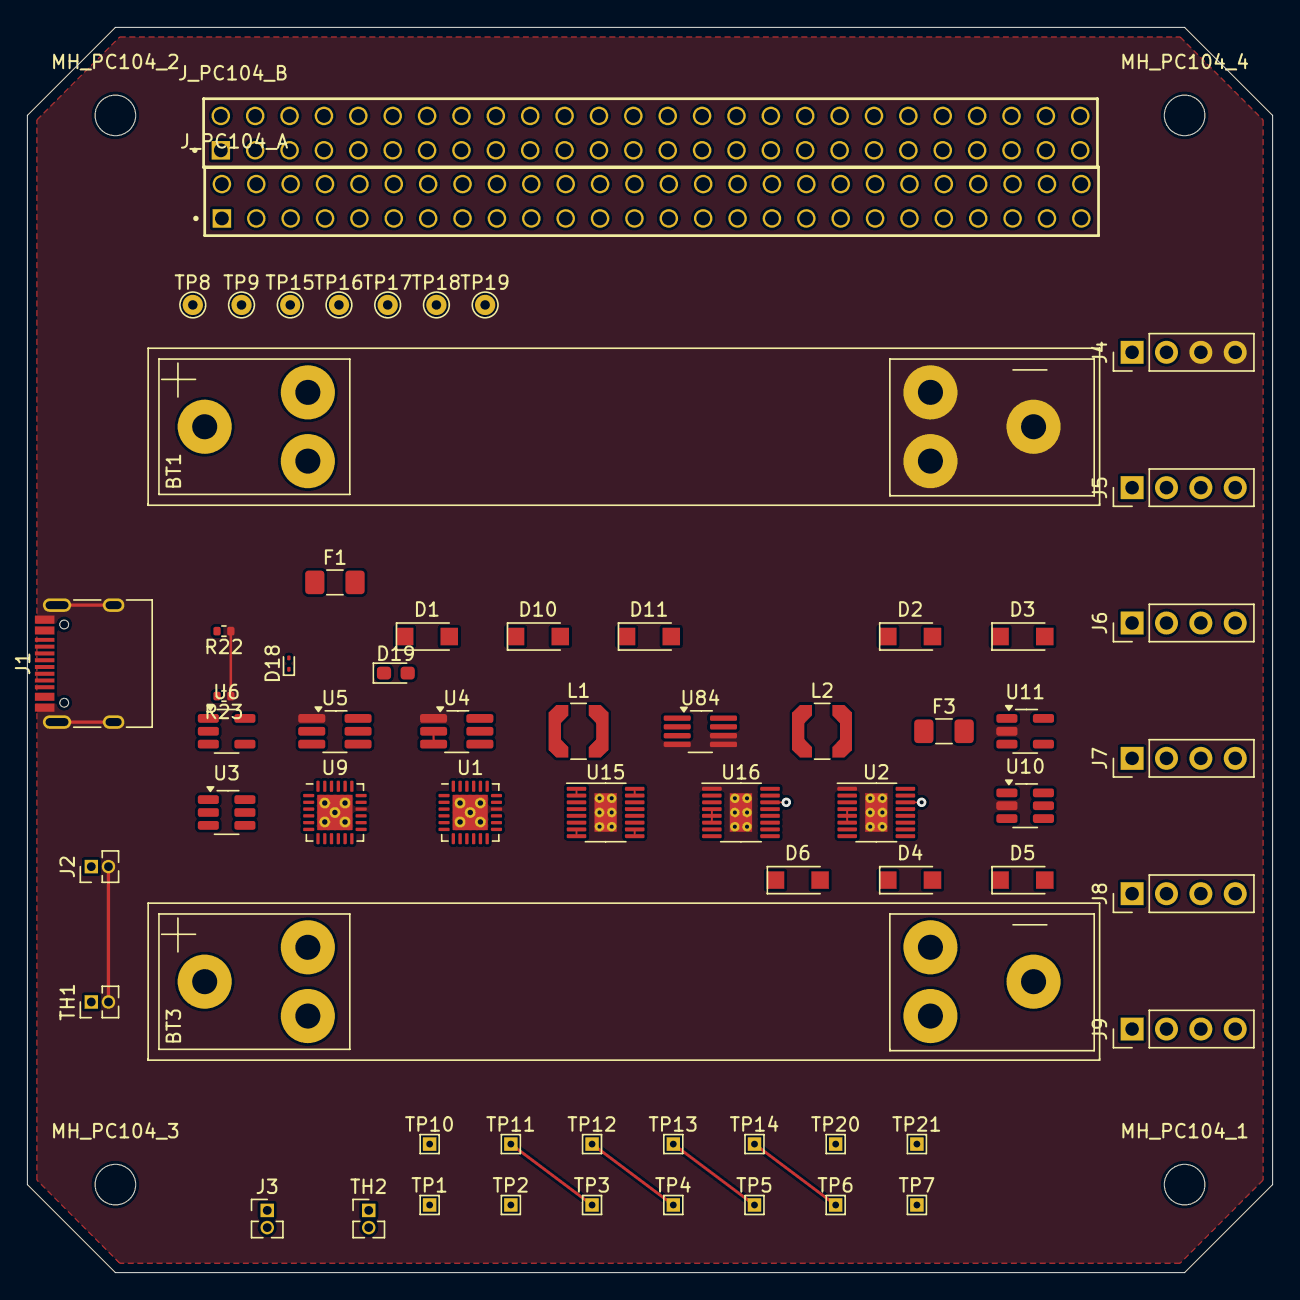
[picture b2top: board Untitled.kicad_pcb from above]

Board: 4 copper layers, 92.0 x 92.0 mm, 68 parts (0 on the bottom side), 25 nets.

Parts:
BT1, BT3: Battery_Cell; BatteryHolder_Keystone_54_v2_1x18650
D1, D2, D3, D4, D5, D6, D10, D11: NRVB120VLSFT1G; D_SOD-123FL_handsolder
D18: ESD9B5.0ST5G; D_SOD-923
D19: LED_SMD_RED; LED_0603_1608Metric_Pad1.05x0.95mm_HandSolder
F1, F3: Polyfuse; Fuse_1206_3216Metric_Pad1.42x1.75mm_HandSolder
J1: USB_C_Receptacle_USB2.0_16P; USB_C_Receptacle_HRO_TYPE-C-31-M-12
J2, J3: Conn_01x02_Female; PinHeader_1x02_P1.27mm_Vertical
J4, J5, J6, J7, J8, J9: Conn_01x04; PinHeader_1x04_P2.54mm_Vertical
J_PC104_A, J_PC104_B: TSW-126-08-G-D; SAMTEC_TSW-126-08-G-D
L1, L2: 4.7uH; L_Coilcraft_LPS4018
MH_PC104_1, MH_PC104_2, MH_PC104_3, MH_PC104_4: MountingHole_3mm
R22, R23: 5.1k; R_0402_1005Metric
TH1, TH2: Thermistor_NTC; PinHeader_1x02_P1.27mm_Vertical
TP1, TP2, TP3, TP4, TP5, TP6, TP7, TP10, TP11, TP12, TP13, TP14, TP20, TP21: TP_1x1; TestPoint_THTPad_1.0x1.0mm_Drill0.5mm
TP8, TP9, TP15, TP16, TP17, TP18, TP19: TestPoint; TestPoint_THTPad_D1.5mm_Drill0.7mm
U1, U9: LTC4066; QFN-24-1EP_4x4mm_P0.5mm_EP2.6x2.6mm_0.4mmThermalVias
U2, U16: LTC3130-1; MSOP-16-1EP_3x4.039mm_P0.5mm_EP1.651x2.845mm_0.3mmThermalVi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
U3, U10: MCP65R46; SOT-23-6_Handsoldering
U4, U5: TPS270; TSOT-23-6_HandSoldering
U6, U11: FPF2123; SOT-23-5_HandSoldering
U15: LTC4415; MSOP-16-1EP_3x4.039mm_P0.5mm_EP1.651x2.845mm_0.3mmThermalVi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
U84: MP3414A; TSOT-23-8_HandSoldering

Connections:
+3.3V: U4.2, U4.3
BAT: U1.2, U1.4, U1.5, U9.2, U9.4, U9.5
CLDIS: TP1.1, U1.10
GND: BT1.2, J1.A1, J1.A12, J1.B1, J1.B12, J1.S1, J2.2, J4.3, J4.4, R22.1, R23.1, TH1.2, U1.16, U1.25, U2.1, U2.17, U4.1, U5.1, U9.16, U9.25, U10.2, U11.2, U15.17, U16.1, U16.17, U84.4, U84.5, U84.6
ISTAT: U1.24, U9.24
MPPC: U2.8, U16.8
NTC: TH1.1, U1.14, U9.14, U10.4
unnamed: J1.A5, R22.2
unnamed: J1.B5, R23.2
PGOOD: U2.13, U16.13
POL: TP4.1, TP12.1, U1.19, U9.19
SHDN: TP3.1, TP11.1, U1.12, U9.12
SUSP: TP2.1, U1.11
VBUS: J1.A4, J1.A9, J1.B4, J1.B9
VCC: U2.7, U16.7
VHEAT: U10.6, U11.1
VIN: U1.9, U2.4, U2.5, U2.6, U9.9, U16.4, U16.5, U16.6, U84.1
VIN1: U15.1, U15.2
VIN2: U15.7, U15.8
VNTC: U1.15, U9.15
VOUT: D1.1, D11.1, U1.1, U1.3, U1.8, U2.14, U9.1, U9.3, U9.8, U16.14, U84.2
VOUT1: U15.15, U15.16
VOUT2: U15.9, U15.10
~ACPR: TP6.1, TP14.1, U1.17, U9.17
~CHRG: TP5.1, TP13.1, U1.18, U9.18

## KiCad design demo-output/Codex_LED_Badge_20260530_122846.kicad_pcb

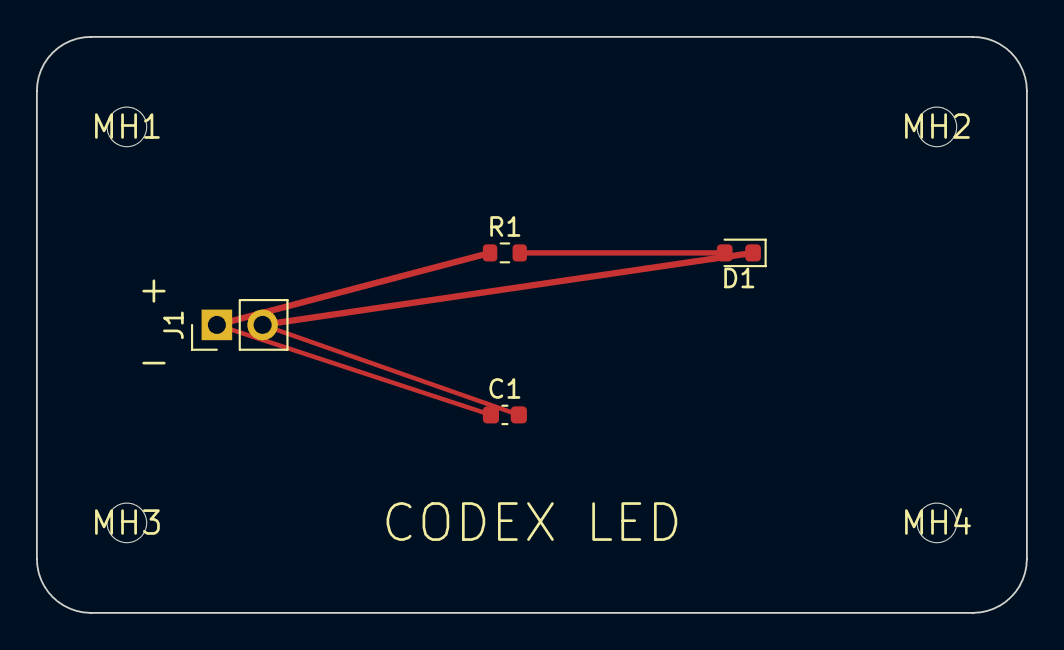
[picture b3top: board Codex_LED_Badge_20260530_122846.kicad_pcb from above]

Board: 2 copper layers, 55.0 x 32.0 mm, 8 parts (0 on the bottom side), 3 nets.

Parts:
C1: 100n; C_0603_1608Metric
D1: LED; LED_0603_1608Metric
J1: PWR; PinHeader_1x02_P2.54mm_Vertical
MH1, MH2, MH3, MH4: MountingHole_2.2mm
R1: 330R; R_0603_1608Metric

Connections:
GND: C1.2, D1.1, J1.2
LED_A: D1.2, R1.2
VCC: C1.1, J1.1, R1.1

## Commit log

2026-05-30 openai substituted for claude and first project in demo-output
2026-05-31 Added feedback loops involving snapshots of schematics and PCB design

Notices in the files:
README.md:
License:
This project is licensed under the MIT License. See [LICENSE](LICENSE) for details.
Citation:
If you use this project in your research or publication, please cite:
@software{kicad_mcp_server,
title = {KiCAD MCP Server: AI-Assisted PCB Design},
author = {mixelpixx},
year = {2025},
url = {https://github.com/mixelpixx/KiCAD-MCP-Server},
version = {2.2.3}
parts and their libraries:
COPYRIGHT: Copyright (C) 2024 Ultra Librarian. All rights reserved.
